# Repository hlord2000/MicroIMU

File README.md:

# A 9-DoF IMU for the Teensy 4.1

Pins:
3.3V->P26 and GND->P40

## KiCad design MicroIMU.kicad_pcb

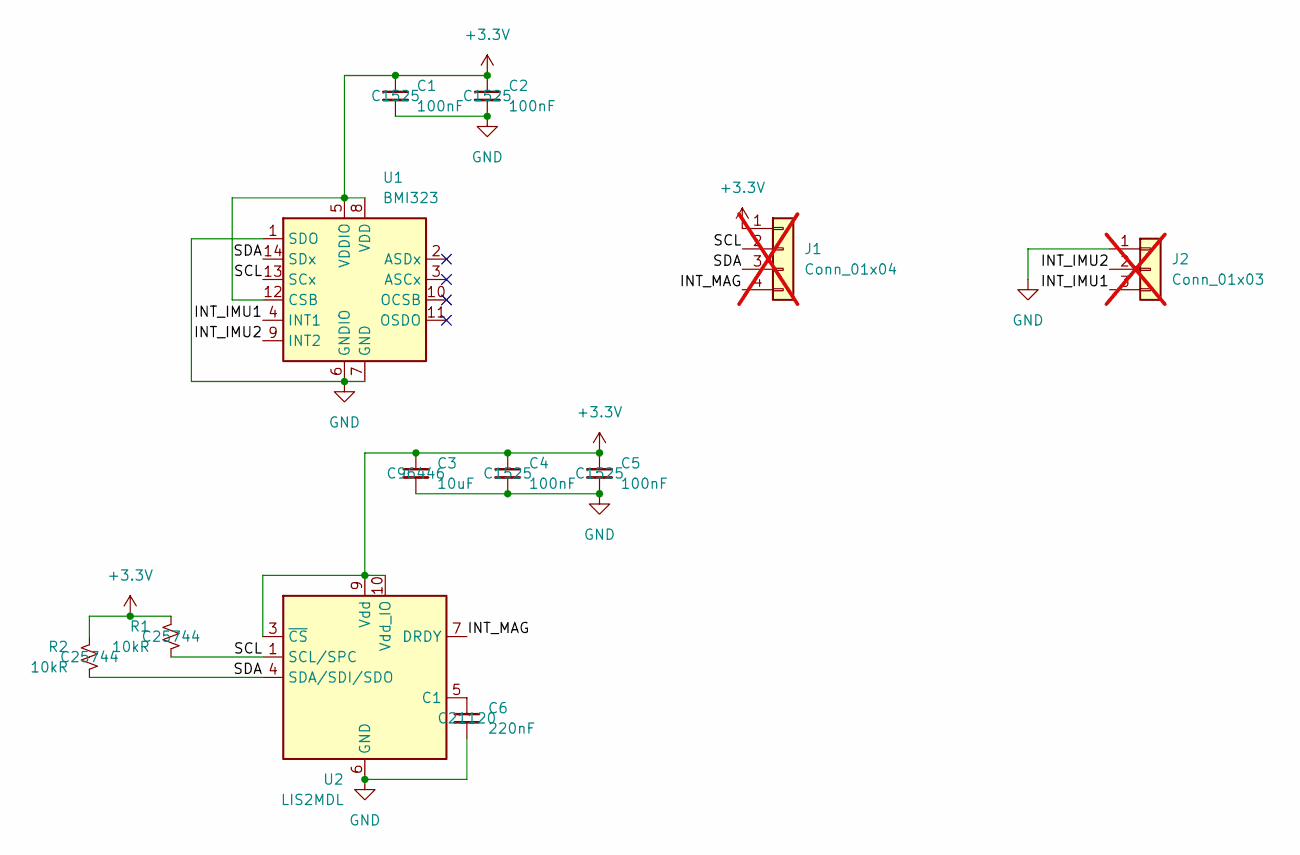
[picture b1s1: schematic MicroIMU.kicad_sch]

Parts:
C1, C2, C4, C5: 100nF; C_0402_1005Metric; LCSC C1525
C3: 10uF; C_0603_1608Metric; LCSC C96446
C6: 220nF; C_0402_1005Metric; LCSC C21120
J1: Conn_01x04; PinSocket_1x04_P2.54mm_Vertical; not fitted
J2: Conn_01x03; PinSocket_1x03_P2.54mm_Vertical; not fitted
R1, R2: 10kR; R_0402_1005Metric; LCSC C25744
U1: BMI323; Bosch_LGA-14_3x2.5mm_P0.5mm; LCSC C5368700
U2: LIS2MDL; LGA-12_2x2mm_P0.5mm; LCSC C919695

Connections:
+3.3V: C1.1, C2.1, C3.1, C4.1, C5.1, J1.1, R1.2, R2.2, U1.5 (VDDIO), U1.8 (VDD), U1.12 (CSB), U2.3 (~CS), U2.9 (Vdd), U2.10 (Vdd_IO)
/INT_IMU1: J2.3, U1.4 (INT1)
/INT_IMU2: J2.2, U1.9 (INT2)
/INT_MAG: J1.4, U2.7 (DRDY)
/SCL: J1.2, R1.1, U1.13 (SCx), U2.1 (SCL/SPC)
/SDA: J1.3, R2.1, U1.14 (SDx), U2.4 (SDA/SDI/SDO)
GND: C1.2, C2.2, C3.2, C4.2, C5.2, C6.2, J2.1, U1.1 (SDO), U1.6 (GNDIO), U1.7 (GND), U2.6 (GND), U2.8 (GND)
unnamed: C6.1, U2.5 (C1)

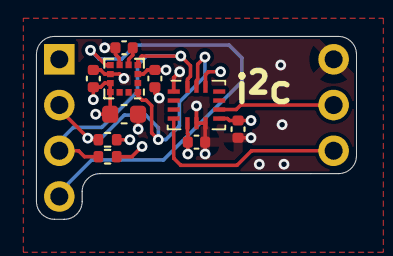
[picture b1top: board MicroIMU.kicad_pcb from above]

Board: 4 copper layers, 17.8 x 10.2 mm, 12 parts (0 on the bottom side), 8 nets.

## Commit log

2024-11-26 Initial commit.
2024-11-26 Added image
